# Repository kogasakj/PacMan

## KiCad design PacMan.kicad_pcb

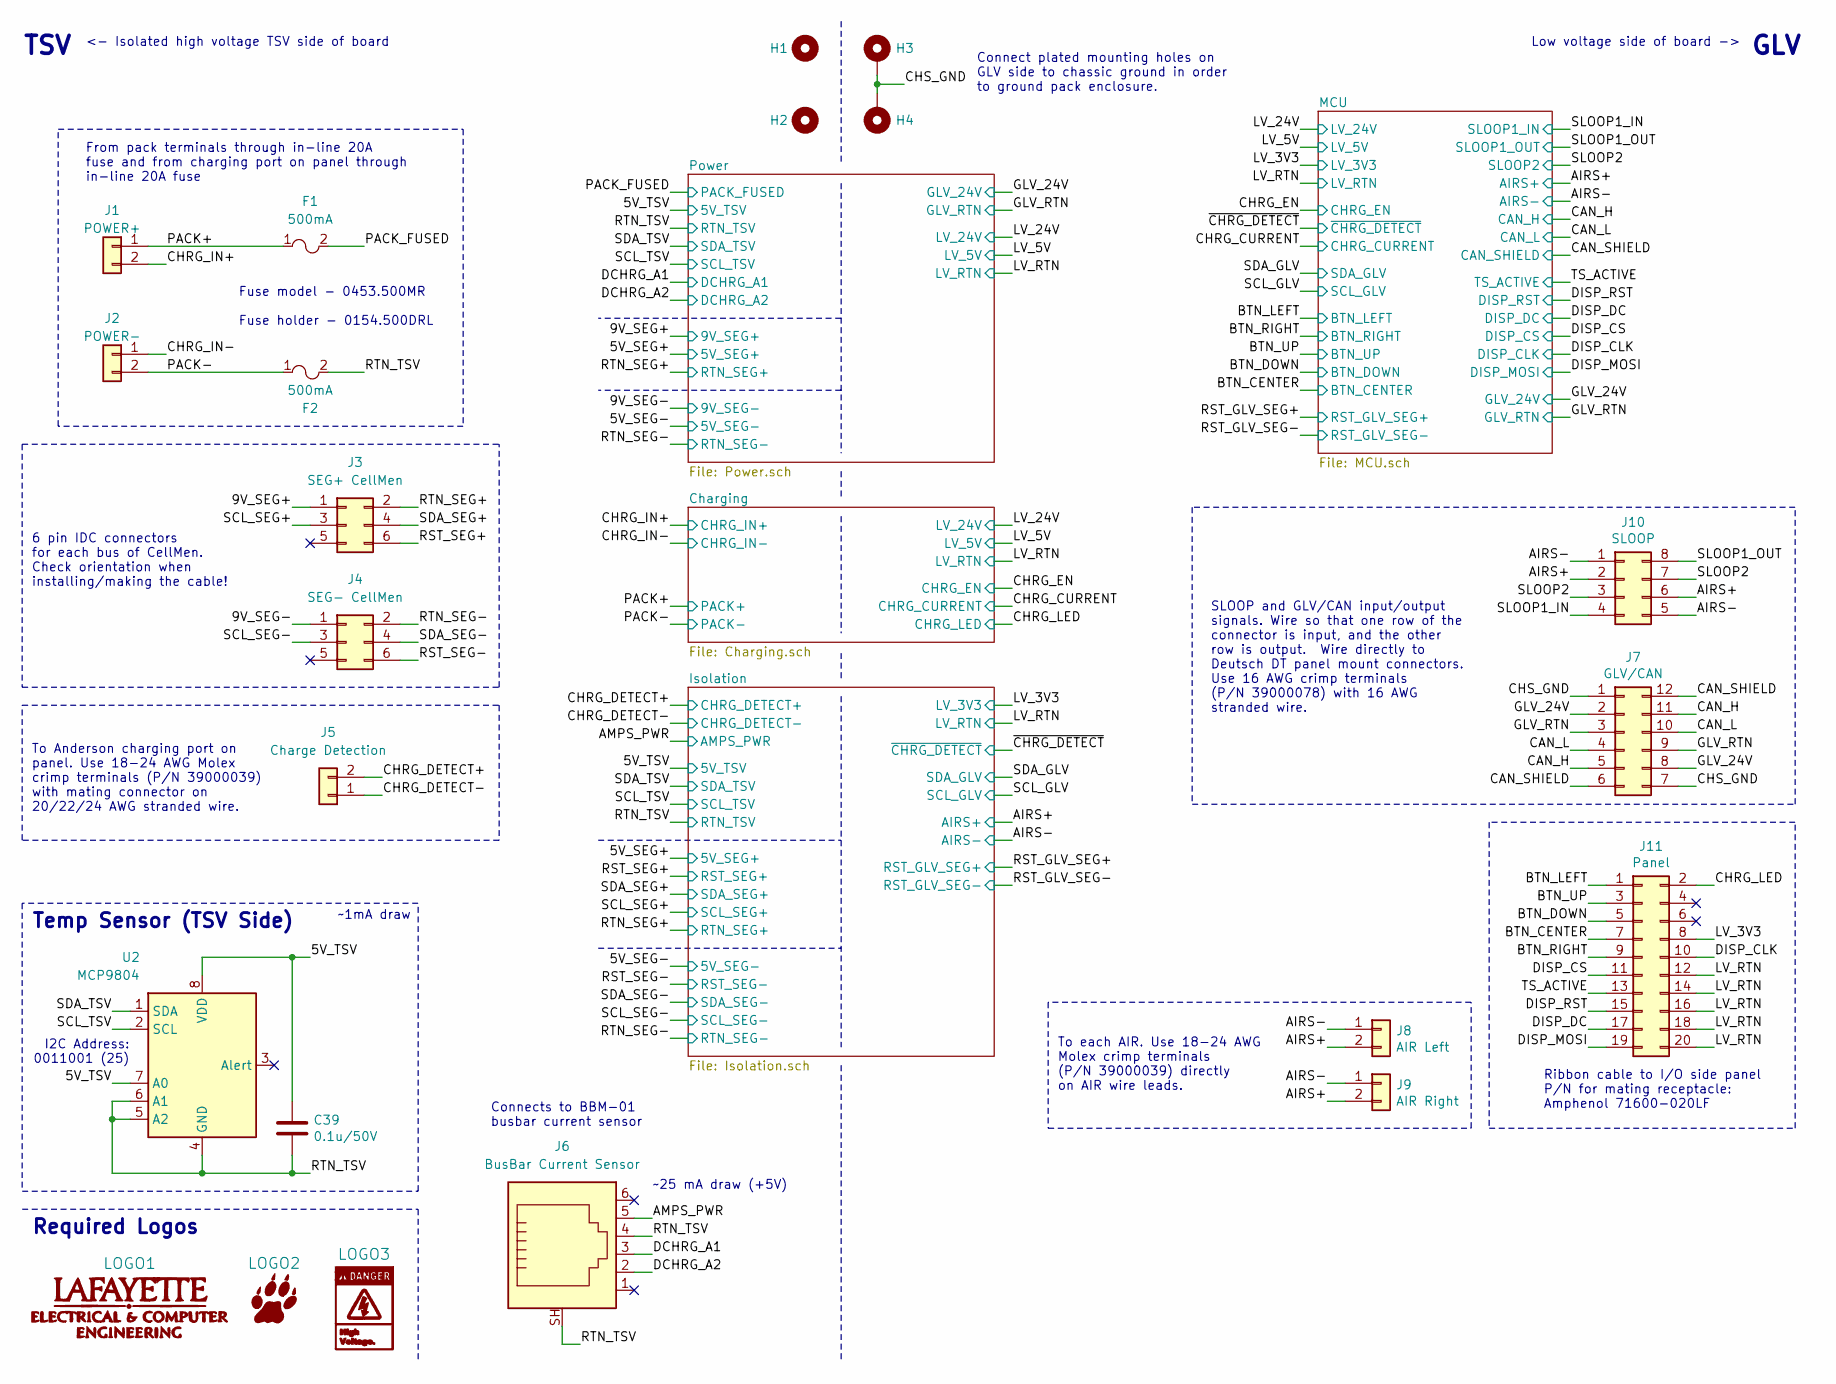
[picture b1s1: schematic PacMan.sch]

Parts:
C39: 0.1u/50V; C_0805_2012Metric_Pad1.15x1.40mm_HandSolder; Manufacturer Part CL21B104KBCNNNC
F1, F2: 500mA; 0154.500DRL; Manufacturer Part 0154.500DRL
H1, H2: MountingHole_NoPad_#4; MountingHole_#4_NoPad
H3, H4: MountingHole_Pad_#4; MountingHole_#4_Pad
J1: POWER+; Powerpole_PP45_FP_1x2; Manufacturer Part 1327FP
J2: POWER-; Powerpole_PP45_FP_1x2; Manufacturer Part 1327G6FP
J3: SEG+ CellMen; IDC-Header_2x03_P2.54mm_Vertical; Manufacturer Part 75869-131LF
J4: SEG- CellMen; IDC-Header_2x03_P2.54mm_Vertical; Manufacturer Part 75869-131LF
J5: Charge Detection; Molex_Mini-Fit_Jr_5566-02A_2x01_P4.20mm_Vertical; Manufacturer Part 1724470202
J6: BusBar Current Sensor; MOLEX_RJ11; Manufacturer Part 0855135002
J7: GLV/CAN; Molex_Mini-Fit_Jr_5566-12A_2x06_P4.20mm_Vertical; Manufacturer Part 0039281123
J8: AIR Left; Molex_Mini-Fit_Jr_5566-02A_2x01_P4.20mm_Vertical; Manufacturer Part 1724470202
J9: AIR Right; Molex_Mini-Fit_Jr_5566-02A_2x01_P4.20mm_Vertical; Manufacturer Part 1724470202
J10: SLOOP; Molex_Mini-Fit_Jr_5566-08A_2x04_P4.20mm_Vertical; Manufacturer Part 0039281083
J11: Panel; Amphenol_IDC-Header_2x10_P2.54mm_Vertical; Manufacturer Part 75869-304LF
LOGO1: LafECEDepLogo; ECE_Logo_Jon
LOGO2: LeopardPawLogo; paw_solder_mask_bigly
LOGO3: DangerHighVoltageLogo; highvoltagesmall
U2: MCP9804; MSOP-8_3x3mm_P0.65mm; Manufacturer Part MCP9804T-E/MS

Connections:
/5V_TSV: C39.1, U2.7 (A0), U2.8 (VDD); also elsewhere on the board
/9V_SEG+: J3.1; also elsewhere on the board
/9V_SEG-: J4.1; also elsewhere on the board
/AIRS+: J8.2, J9.2, J10.2, J10.6; also elsewhere on the board
/AIRS-: J8.1, J9.1, J10.1, J10.5; also elsewhere on the board
/AMPS_PWR: J6.5; also elsewhere on the board
/BTN_CENTER: J11.7; also elsewhere on the board
/BTN_DOWN: J11.5; also elsewhere on the board
/BTN_LEFT: J11.1; also elsewhere on the board
/BTN_RIGHT: J11.9; also elsewhere on the board
/BTN_UP: J11.3; also elsewhere on the board
/CAN_H: J7.5, J7.11; also elsewhere on the board
/CAN_L: J7.4, J7.10; also elsewhere on the board
/CAN_SHIELD: J7.6, J7.12; also elsewhere on the board
/CHRG_DETECT+: J5.2; also elsewhere on the board
/CHRG_DETECT-: J5.1; also elsewhere on the board
/CHRG_IN+: J1.2; also elsewhere on the board
/CHRG_IN-: J2.1; also elsewhere on the board
/CHRG_LED: J11.2; also elsewhere on the board
/CHS_GND: H3.1, H4.1, J7.1, J7.7
/DCHRG_A1: J6.3; also elsewhere on the board
/DCHRG_A2: J6.2; also elsewhere on the board
/DISP_CLK: J11.10; also elsewhere on the board
/DISP_CS: J11.11; also elsewhere on the board
/DISP_DC: J11.17; also elsewhere on the board
/DISP_MOSI: J11.19
/DISP_RST: J11.15; also elsewhere on the board
/GLV_24V: J7.2, J7.8; also elsewhere on the board
/GLV_RTN: J7.3, J7.9, J11.12, J11.14, J11.16, J11.18, J11.20; also elsewhere on the board
/LV_3V3: J11.8; also elsewhere on the board
/PACK+: F1.1, J1.1; also elsewhere on the board
/PACK-: F2.1, J2.2; also elsewhere on the board
/PACK_FUSED: F1.2; also elsewhere on the board
/RST_SEG+: J3.6; also elsewhere on the board
/RST_SEG-: J4.6; also elsewhere on the board
/RTN_SEG+: J3.2; also elsewhere on the board
/RTN_SEG-: J4.2; also elsewhere on the board
/RTN_TSV: C39.2, F2.2, J6.4, J6.SH, U2.4 (GND), U2.5 (A2), U2.6 (A1); also elsewhere on the board
/SCL_SEG+: J3.3; also elsewhere on the board
/SCL_SEG-: J4.3; also elsewhere on the board
/SCL_TSV: U2.2 (SCL); also elsewhere on the board
/SDA_SEG+: J3.4; also elsewhere on the board
/SDA_SEG-: J4.4; also elsewhere on the board
/SDA_TSV: U2.1 (SDA); also elsewhere on the board
/SLOOP1_IN: J10.4; also elsewhere on the board
/SLOOP1_OUT: J10.8; also elsewhere on the board
/SLOOP2: J10.3, J10.7; also elsewhere on the board
/TS_ACTIVE: J11.13

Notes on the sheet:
GLV
TSV
Ribbon cable to I/O side panel P/N for mating receptacle: Amphenol 71600-020LF
From pack terminals through in-line 20A fuse and from charging port on panel through in-line 20A fuse
6 pin IDC connectors for each bus of CellMen. Check orientation when installing/making the cable!
To Anderson charging port on panel. Use 18-24 AWG Molex crimp terminals (P/N 39000039) with mating connector on 20/22/24 AWG stranded wire.
I2C Address: 0011001 (25)
Temp Sensor (TSV Side)
~~1mA draw
<- Isolated high voltage TSV side of board
Low voltage side of board ->
Required Logos
Fuse model - 0453.500MR Fuse holder - 0154.500DRL
~~25 mA draw (+5V)
Connects to BBM-01 busbar current sensor
To each AIR. Use 18-24 AWG Molex crimp terminals (P/N 39000039) directly on AIR wire leads.
SLOOP and GLV/CAN input/output signals. Wire so that one row of the connector is input, and the other row is output. Wire directly to Deutsch DT panel mount connectors. Use 16 AWG crimp terminals (P/N 39000078) with 16 AWG stranded wire.
Connect plated mounting holes on GLV side to chassic ground in order to ground pack enclosure.

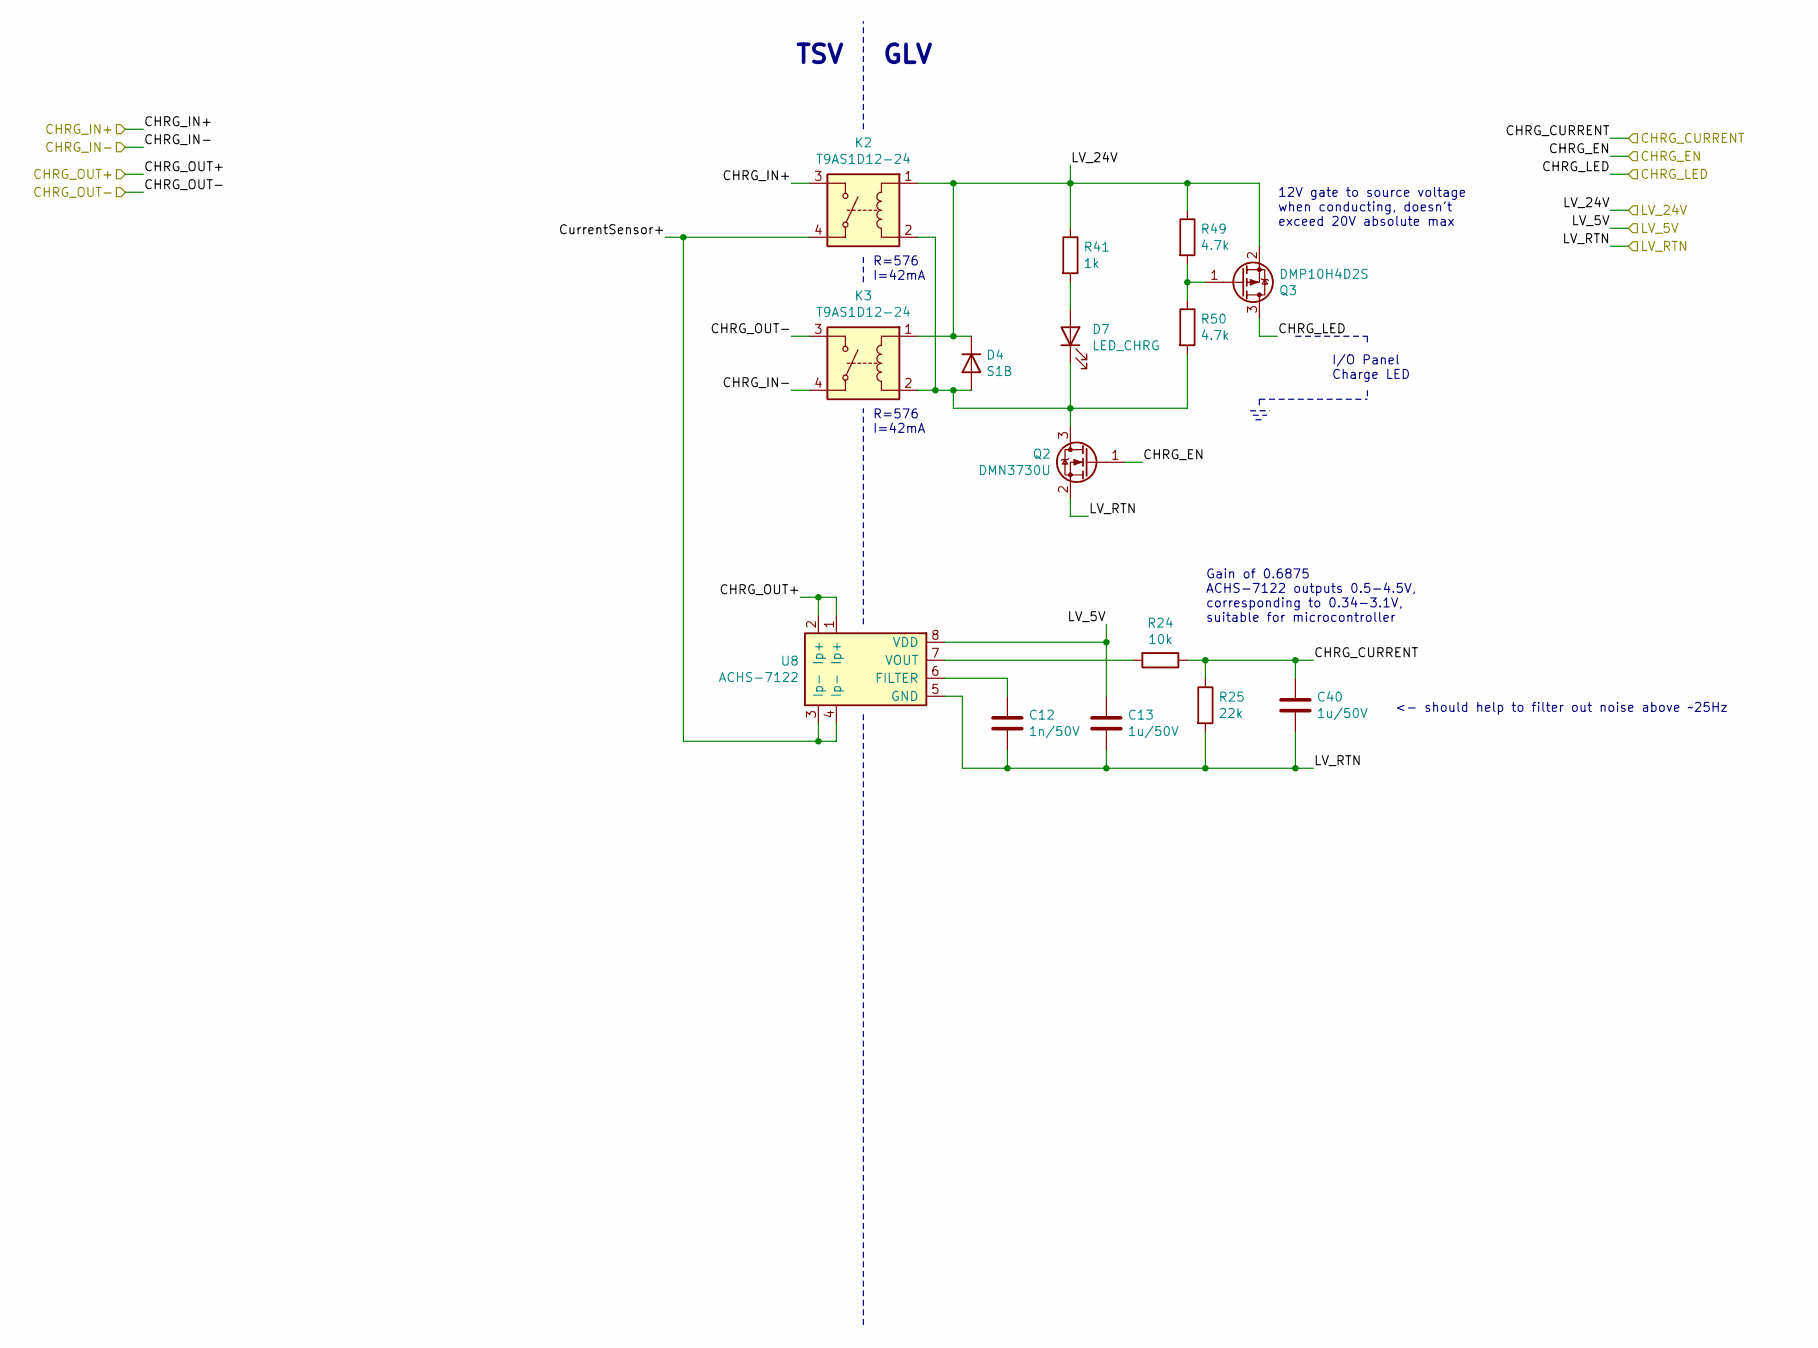
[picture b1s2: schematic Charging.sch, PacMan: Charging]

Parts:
C12: 1n/50V; C_0805_2012Metric_Pad1.15x1.40mm_HandSolder; Manufacturer Part CL21B102KBCNNNC
C13, C40: 1u/50V; C_0805_2012Metric_Pad1.15x1.40mm_HandSolder; Manufacturer Part CL21B105KBFNNNG
D4: S1B; D_SMA_Handsoldering; Manufacturer Part S1B-13-F
D7: LED_CHRG; LED_0805_2012Metric_Pad1.15x1.40mm_HandSolder; Manufacturer Part LTST-C171AKT
K2, K3: T9AS1D12-24; T9AS1D12; Manufacturer Part T9AS1D12-24
Q2: DMN3730U; SOT-23; Manufacturer Part DMN3730U-7
Q3: DMP10H4D2S; SOT-23; Manufacturer Part DMP10H4D2S-7
R24: 10k; R_0805_2012Metric_Pad1.15x1.40mm_HandSolder
R25: 22k; R_0805_2012Metric_Pad1.15x1.40mm_HandSolder
R41: 1k; R_0805_2012Metric_Pad1.15x1.40mm_HandSolder
R49, R50: 4.7k; R_0805_2012Metric_Pad1.15x1.40mm_HandSolder
U8: ACHS-7122; SO-8_3.9x4.9mm_P1.27mm; Manufacturer Part ACHS-7122-000E

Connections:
/CHRG_CURRENT: C40.1, R24.1, R25.1; also elsewhere on the board
/CHRG_EN: Q2.1 (G); also elsewhere on the board
/CHRG_IN+: K2.3; also elsewhere on the board
/CHRG_IN-: K3.4; also elsewhere on the board
/CHRG_LED: Q3.3 (D); also elsewhere on the board
/Charging/CurrentSensor+: K2.4, U8.3 (Ip-), U8.4 (Ip-)
/GLV_RTN: C12.2, C13.2, C40.2, Q2.2 (S), R25.2, U8.5 (GND); also elsewhere on the board
/LV_5V: C13.1, U8.8 (VDD); also elsewhere on the board
/LV_24V: D4.1 (K), K2.1, K3.1, Q3.2 (S), R41.1, R49.1; also elsewhere on the board
/PACK+: U8.1 (Ip+), U8.2 (Ip+); also elsewhere on the board
/PACK-: K3.3; also elsewhere on the board
unnamed: C12.1, U8.6 (FILTER)
unnamed: D4.2 (A), D7.1 (K), K2.2, K3.2, Q2.3 (D), R50.2
unnamed: D7.2 (A), R41.2
unnamed: Q3.1 (G), R49.2, R50.1
unnamed: R24.2, U8.7 (VOUT)

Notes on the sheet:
GLV
TSV
R=576 I=42mA
I/O Panel Charge LED
Gain of 0.6875 ACHS-7122 outputs 0.5-4.5V, corresponding to 0.34-3.1V, suitable for microcontroller
<- should help to filter out noise above ~~25Hz
12V gate to source voltage when conducting, doesn't exceed 20V absolute max

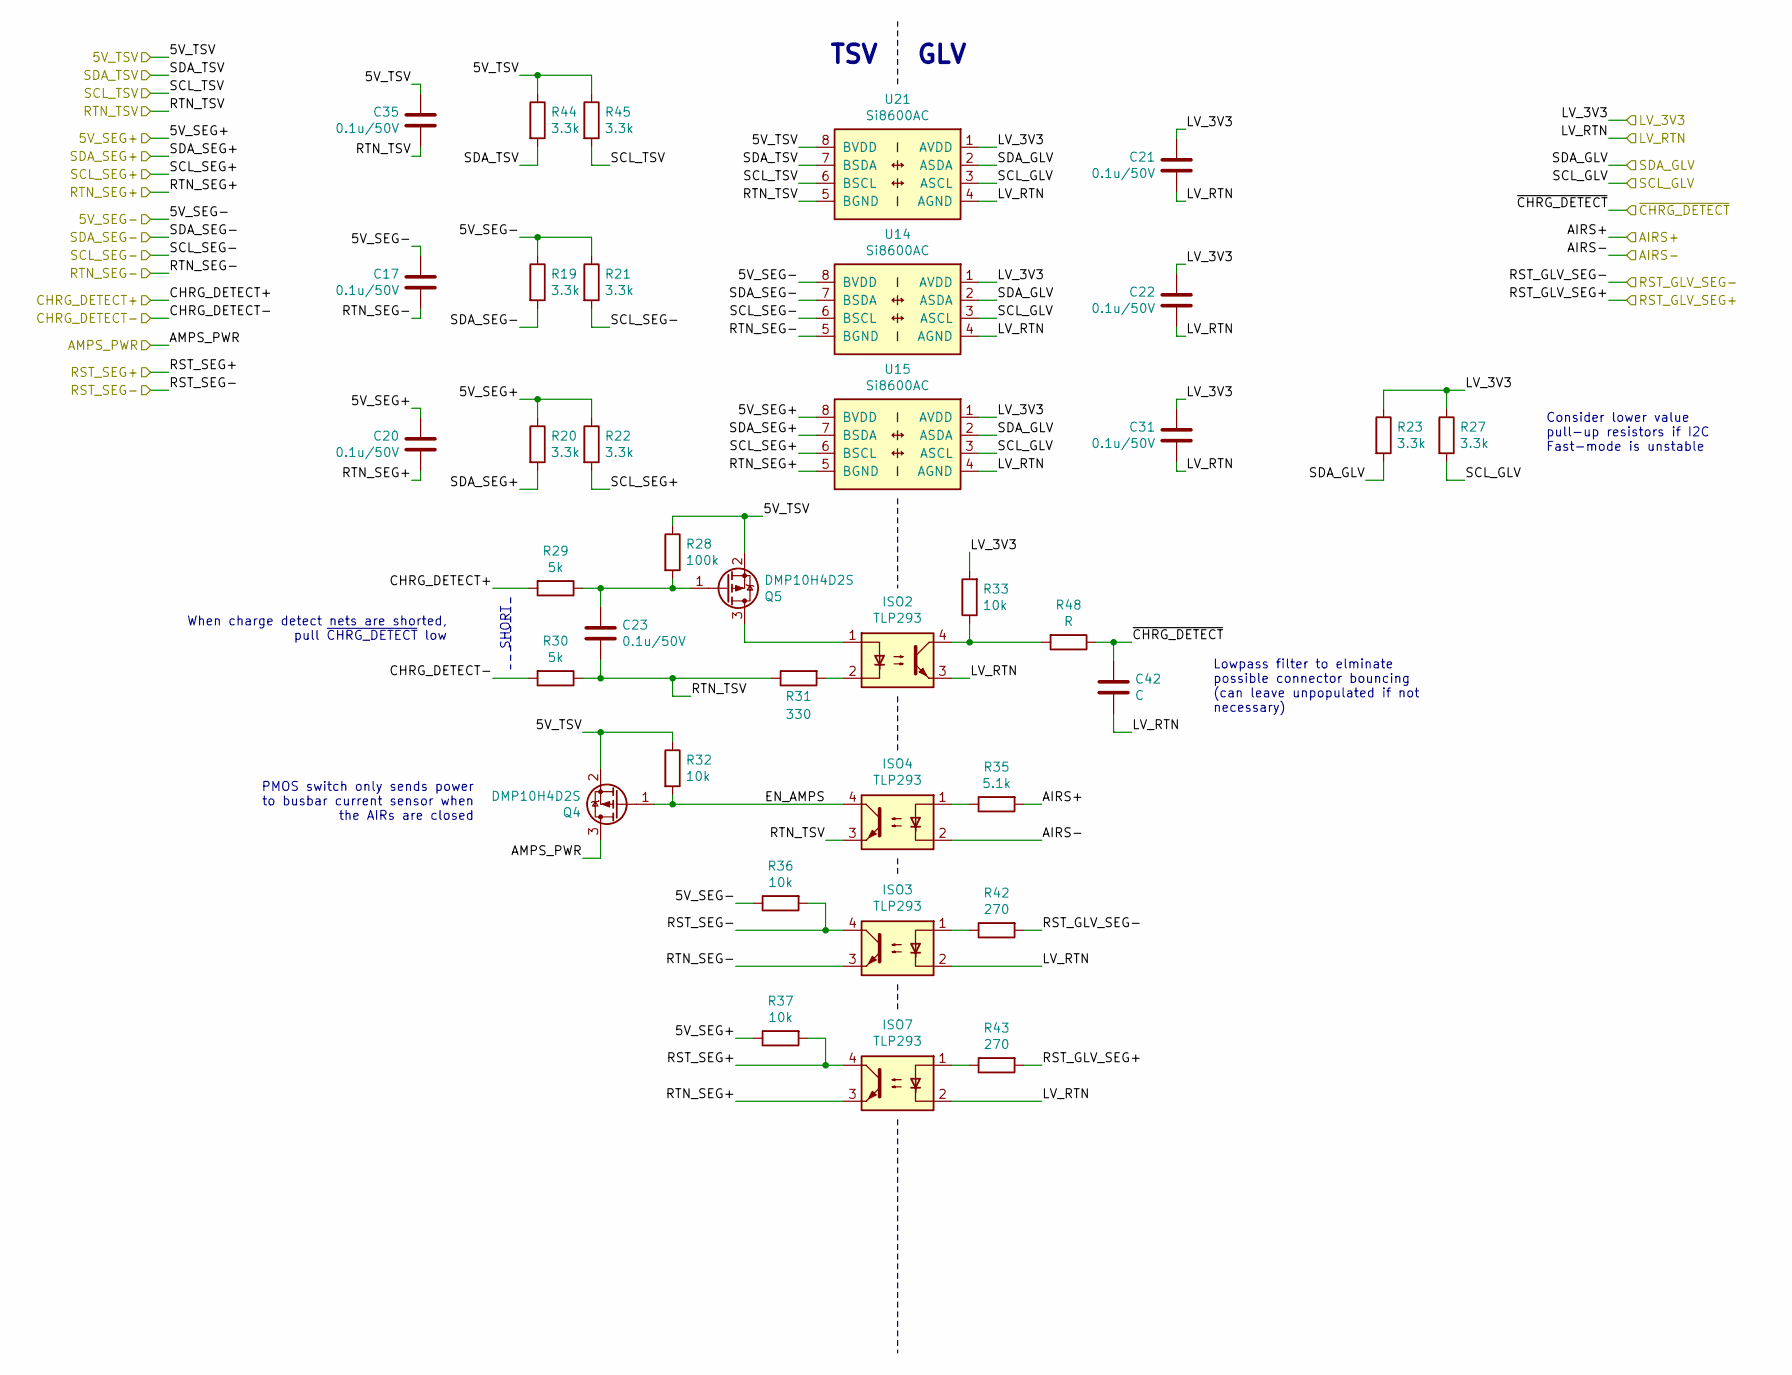
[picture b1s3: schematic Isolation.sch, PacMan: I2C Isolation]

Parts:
C17, C20, C21, C22, C23, C31, C35: 0.1u/50V; C_0805_2012Metric_Pad1.15x1.40mm_HandSolder; Manufacturer Part CL21B104KBCNNNC
C42: C; C_0805_2012Metric_Pad1.15x1.40mm_HandSolder
ISO2, ISO3, ISO4, ISO7: TLP293; SO-4_4.4x2.3mm_P1.27mm; Manufacturer Part TLP293(GR-TPL,E
Q4, Q5: DMP10H4D2S; SOT-23; Manufacturer Part DMP10H4D2S-7
R19, R20, R21, R22, R23, R27, R44, R45: 3.3k; R_0805_2012Metric_Pad1.15x1.40mm_HandSolder
R28: 100k; R_0805_2012Metric_Pad1.15x1.40mm_HandSolder
R29, R30: 5k; R_0805_2012Metric_Pad1.15x1.40mm_HandSolder
R31: 330; R_0805_2012Metric_Pad1.15x1.40mm_HandSolder
R32, R33, R36, R37: 10k; R_0805_2012Metric_Pad1.15x1.40mm_HandSolder
R35: 5.1k; R_0805_2012Metric_Pad1.15x1.40mm_HandSolder
R42, R43: 270; R_0805_2012Metric_Pad1.15x1.40mm_HandSolder
R48: R; R_0805_2012Metric_Pad1.15x1.40mm_HandSolder
U14, U15, U21: Si8600AC; SO-8_3.9x4.9mm_P1.27mm; Manufacturer Part SI8600AC-B-ISR

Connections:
/5V_SEG+: C20.1, R20.1, R22.1, R37.1, U15.8 (BVDD); also elsewhere on the board
/5V_SEG-: C17.1, R19.1, R21.1, R36.1, U14.8 (BVDD); also elsewhere on the board
/5V_TSV: C35.1, Q4.2 (S), Q5.2 (S), R28.1, R32.1, R44.1, R45.1, U21.8 (BVDD); also elsewhere on the board
/AIRS+: R35.2; also elsewhere on the board
/AIRS-: ISO4.2; also elsewhere on the board
/AMPS_PWR: Q4.3 (D); also elsewhere on the board
/CHRG_DETECT+: R29.2; also elsewhere on the board
/CHRG_DETECT-: R30.2; also elsewhere on the board
/GLV_RTN: C21.2, C22.2, C31.2, C42.2, ISO2.3, ISO3.2, ISO7.2, U14.4 (AGND), U15.4 (AGND), U21.4 (AGND); also elsewhere on the board
/Isolation/EN_AMPS: ISO4.4, Q4.1 (G), R32.2
/LV_3V3: C21.1, C22.1, C31.1, R23.1, R27.1, R33.2, U14.1 (AVDD), U15.1 (AVDD), U21.1 (AVDD); also elsewhere on the board
/RST_GLV_SEG+: R43.2; also elsewhere on the board
/RST_GLV_SEG-: R42.2; also elsewhere on the board
/RST_SEG+: ISO7.4, R37.2; also elsewhere on the board
/RST_SEG-: ISO3.4, R36.2; also elsewhere on the board
/RTN_SEG+: C20.2, ISO7.3, U15.5 (BGND); also elsewhere on the board
/RTN_SEG-: C17.2, ISO3.3, U14.5 (BGND); also elsewhere on the board
/RTN_TSV: C23.2, C35.2, ISO4.3, R30.1, R31.1, U21.5 (BGND); also elsewhere on the board
/SCL_GLV: R27.2, U14.3 (ASCL), U15.3 (ASCL), U21.3 (ASCL); also elsewhere on the board
/SCL_SEG+: R22.2, U15.6 (BSCL); also elsewhere on the board
/SCL_SEG-: R21.2, U14.6 (BSCL); also elsewhere on the board
/SCL_TSV: R45.2, U21.6 (BSCL); also elsewhere on the board
/SDA_GLV: R23.2, U14.2 (ASDA), U15.2 (ASDA), U21.2 (ASDA); also elsewhere on the board
/SDA_SEG+: R20.2, U15.7 (BSDA); also elsewhere on the board
/SDA_SEG-: R19.2, U14.7 (BSDA); also elsewhere on the board
/SDA_TSV: R44.2, U21.7 (BSDA); also elsewhere on the board
/~CHRG_DETECT: C42.1, R48.1; also elsewhere on the board
unnamed: C23.1, Q5.1 (G), R28.2, R29.1
unnamed: ISO2.1, Q5.3 (D)
unnamed: ISO2.2, R31.2
unnamed: ISO2.4, R33.1, R48.2
unnamed: ISO3.1, R42.1
unnamed: ISO4.1, R35.1
unnamed: ISO7.1, R43.1

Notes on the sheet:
GLV
TSV
SHORT
PMOS switch only sends power to busbar current sensor when the AIRs are closed
When charge detect nets are shorted, pull ~CHRG_DETECT low
Lowpass filter to elminate possible connector bouncing (can leave unpopulated if not necessary)
Consider lower value pull-up resistors if I2C Fast-mode is unstable

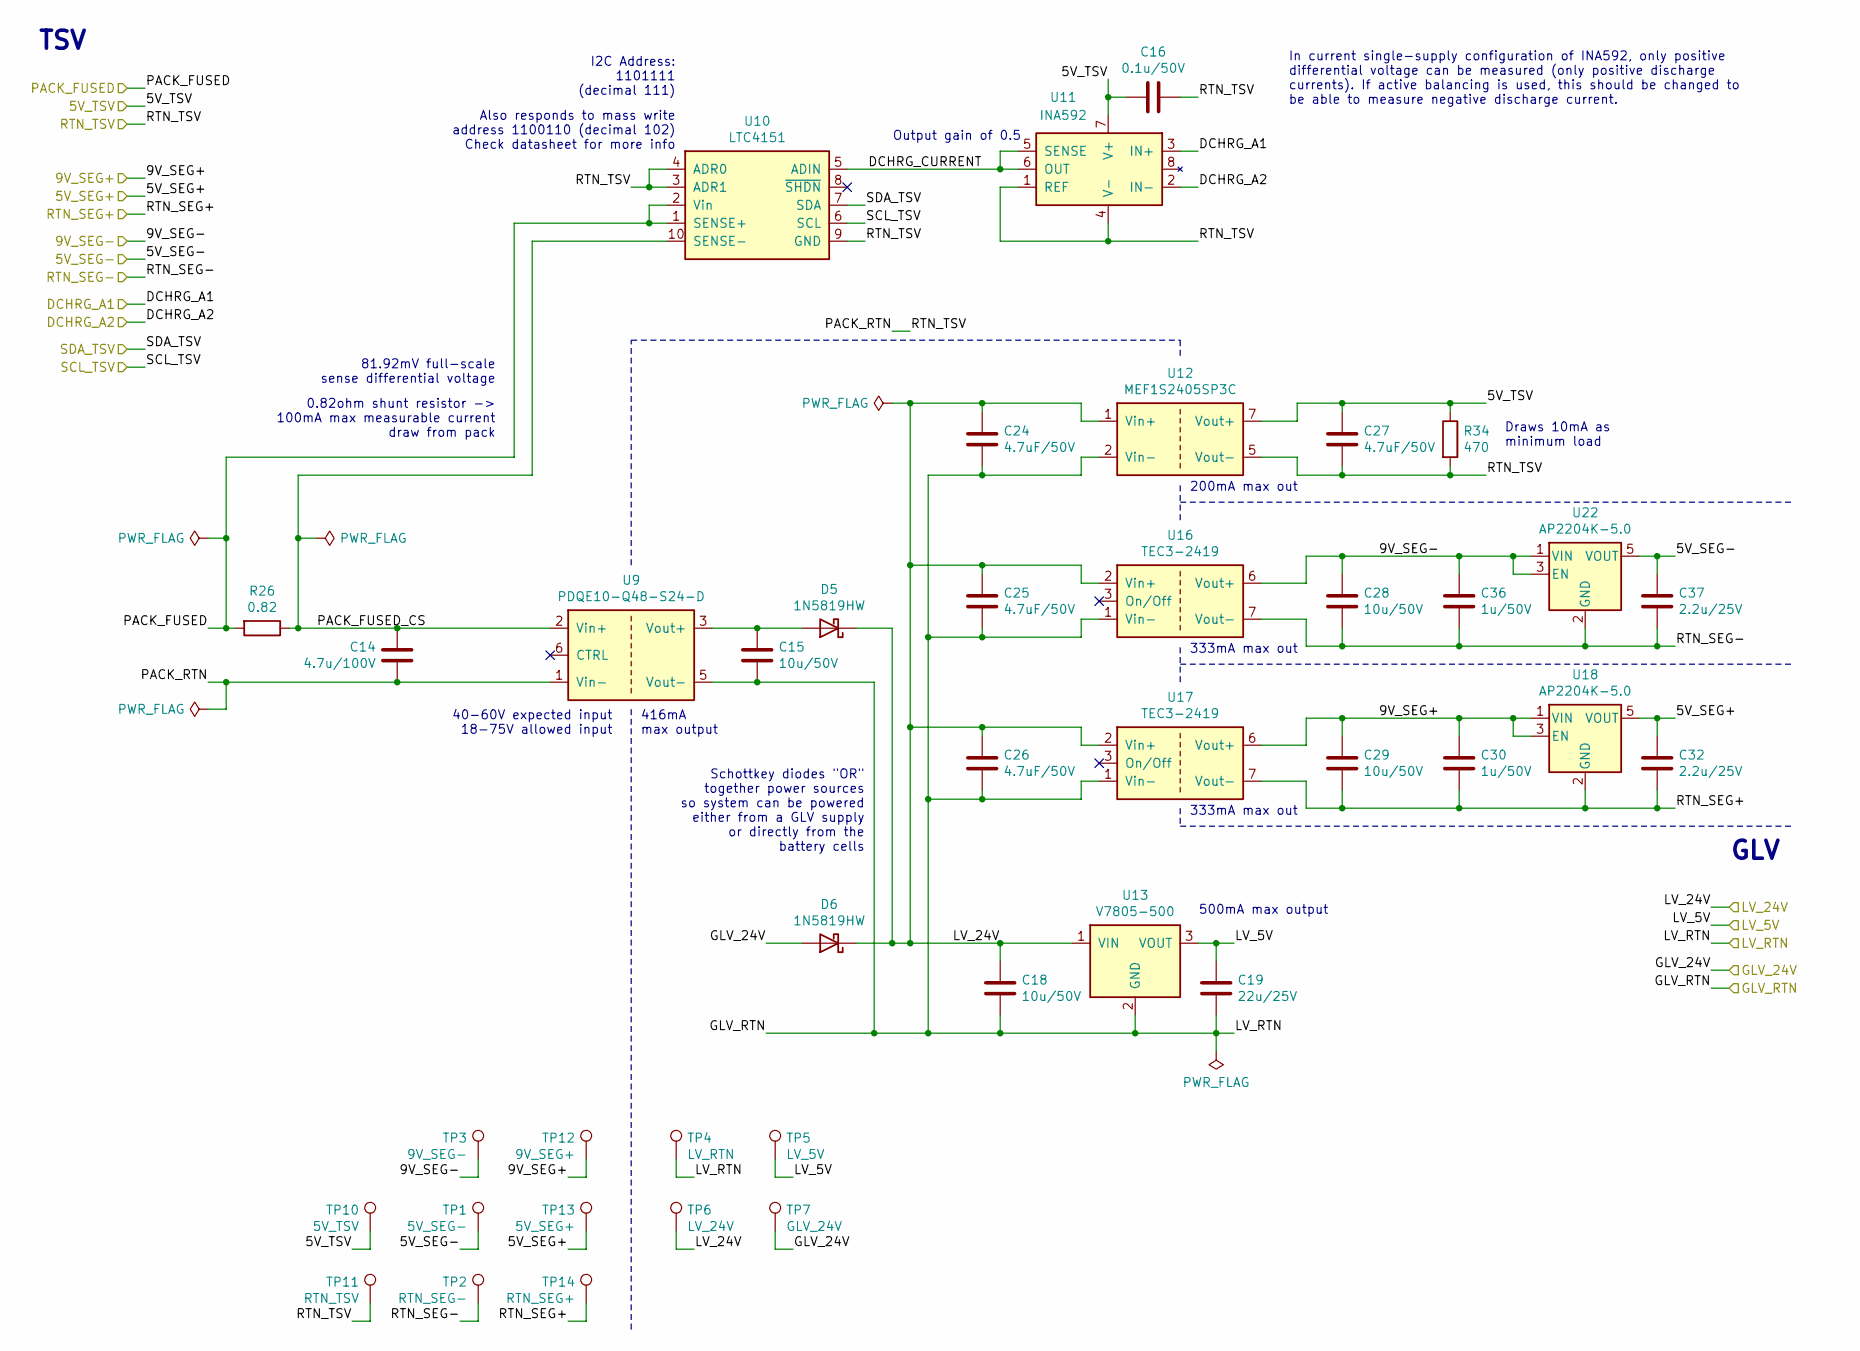
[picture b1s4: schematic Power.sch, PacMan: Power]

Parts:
C14: 4.7u/100V; C_1210_3225Metric_Pad1.42x2.65mm_HandSolder; Manufacturer Part CL32B475KCVZW6E
C15, C18, C28, C29: 10u/50V; C_1210_3225Metric_Pad1.42x2.65mm_HandSolder; Manufacturer Part CL32B106KBJNNWE
C16: 0.1u/50V; C_0805_2012Metric_Pad1.15x1.40mm_HandSolder; Manufacturer Part CL21B104KBCNNNC
C19: 22u/25V; C_1210_3225Metric_Pad1.42x2.65mm_HandSolder; Manufacturer Part CL32B226KAJNFNE
C24, C25, C26, C27: 4.7uF/50V; C_1206_3216Metric_Pad1.42x1.75mm_HandSolder; Manufacturer Part CL31B475KBHNNNE
C30, C36: 1u/50V; C_0805_2012Metric_Pad1.15x1.40mm_HandSolder; Manufacturer Part CL21B105KBFNNNG
C32, C37: 2.2u/25V; C_0805_2012Metric_Pad1.15x1.40mm_HandSolder; Manufacturer Part CL21B225KAFNFNE
D5, D6: 1N5819HW; D_SOD-123; Manufacturer Part 1N5819HW-7-F
R26: 0.82; R_0805_2012Metric_Pad1.15x1.40mm_HandSolder; Manufacturer Part ERJ-6DQFR82V
R34: 470; R_0805_2012Metric_Pad1.15x1.40mm_HandSolder
TP1: 5V_SEG-; TestPoint_Pad_D1.5mm
TP2: RTN_SEG-; R_0805_2012Metric_Pad1.15x1.40mm_HandSolder; Manufacturer Part RCT-0C
TP3: 9V_SEG-; TestPoint_Pad_D1.5mm
TP4: LV_RTN; R_0805_2012Metric_Pad1.15x1.40mm_HandSolder; Manufacturer Part RCT-0C
TP5: LV_5V; TestPoint_Pad_D1.5mm
TP6: LV_24V; TestPoint_Pad_D1.5mm
TP7: GLV_24V; TestPoint_Pad_D1.5mm
TP10: 5V_TSV; TestPoint_Pad_D1.5mm
TP11: RTN_TSV; R_0805_2012Metric_Pad1.15x1.40mm_HandSolder; Manufacturer Part RCT-0C
TP12: 9V_SEG+; TestPoint_Pad_D1.5mm
TP13: 5V_SEG+; TestPoint_Pad_D1.5mm
TP14: RTN_SEG+; R_0805_2012Metric_Pad1.15x1.40mm_HandSolder; Manufacturer Part RCT-0C
U9: PDQE10-Q48-S24-D; PDQE10-DIP6; Manufacturer Part PDQE10-Q48-S24-D
U10: LTC4151; MSOP-10_3x3mm_P0.5mm; Manufacturer Part LTC4151IMS#TRPBF
U11: INA592; VSSOP-8_3.0x3.0mm_P0.65mm; Manufacturer Part INA592IDGKR
U12: MEF1S2405SP3C; Manufacturer Part MEF1S2405SP3C
U13: V7805-500; VX7805-500; Manufacturer Part V7805-500
U16, U17: TEC3-2419; Manufacturer Part TEC 3-2419
U18, U22: AP2204K-5.0; SOT-23-5; Manufacturer Part AP2204K-5.0TRG1

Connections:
/5V_SEG+: C32.1, TP13.1, U18.5 (VOUT); also elsewhere on the board
/5V_SEG-: C37.1, TP1.1, U22.5 (VOUT); also elsewhere on the board
/5V_TSV: C16.2, C27.1, R34.1, TP10.1, U11.7 (V+), U12.7 (Vout+); also elsewhere on the board
/9V_SEG+: C29.1, C30.1, TP12.1, U17.6 (Vout+), U18.1 (VIN), U18.3 (EN); also elsewhere on the board
/9V_SEG-: C28.1, C36.1, TP3.1, U16.6 (Vout+), U22.1 (VIN), U22.3 (EN); also elsewhere on the board
/DCHRG_A1: U11.3 (IN+); also elsewhere on the board
/DCHRG_A2: U11.2 (IN-); also elsewhere on the board
/GLV_24V: D6.2 (A), TP7.1; also elsewhere on the board
/GLV_RTN: C15.2, C18.2, C19.2, C24.2, C25.2, C26.2, TP4.1, U9.5 (Vout-), U12.2 (Vin-), U13.2 (GND), U16.1 (Vin-), U17.1 (Vin-); also elsewhere on the board
/LV_5V: C19.1, TP5.1, U13.3 (VOUT); also elsewhere on the board
/LV_24V: C18.1, C24.1, C25.1, C26.1, D5.1 (K), D6.1 (K), TP6.1, U12.1 (Vin+), U13.1 (VIN), U16.2 (Vin+), U17.2 (Vin+); also elsewhere on the board
/PACK_FUSED: R26.2, U10.1 (SENSE+), U10.2 (Vin); also elsewhere on the board
/Power/DCHRG_CURRENT: U10.5 (ADIN), U11.5 (SENSE), U11.6 (OUT)
/Power/PACK_FUSED_CS: C14.1, R26.1, U9.2 (Vin+), U10.10 (SENSE-)
/RTN_SEG+: C29.2, C30.2, C32.2, TP14.1, U17.7 (Vout-), U18.2 (GND); also elsewhere on the board
/RTN_SEG-: C28.2, C36.2, C37.2, TP2.1, U16.7 (Vout-), U22.2 (GND); also elsewhere on the board
/RTN_TSV: C14.2, C16.1, C27.2, R34.2, TP11.1, U9.1 (Vin-), U10.3 (ADR1), U10.4 (ADR0), U10.9 (GND), U11.1 (REF), U11.4 (V-), U12.5 (Vout-); also elsewhere on the board
/SCL_TSV: U10.6 (SCL); also elsewhere on the board
/SDA_TSV: U10.7 (SDA); also elsewhere on the board
unnamed: C15.1, D5.2 (A), U9.3 (Vout+)

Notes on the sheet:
500mA max output
TSV
GLV
I2C Address: 1101111 (decimal 111)
40-60V expected input 18-75V allowed input
416mA max output
333mA max out
200mA max out
Draws 10mA as minimum load
Schottkey diodes "OR" together power sources so system can be powered either from a GLV supply or directly from the battery cells
81.92mV full-scale sense differential voltage
0.82ohm shunt resistor -> 100mA max measurable current draw from pack
Also responds to mass write address 1100110 (decimal 102) Check datasheet for more info
Output gain of 0.5
In current single-supply configuration of INA592, only positive differential voltage can be measured (only positive discharge currents). If active balancing is used, this should be changed to be able to measure negative discharge current.
